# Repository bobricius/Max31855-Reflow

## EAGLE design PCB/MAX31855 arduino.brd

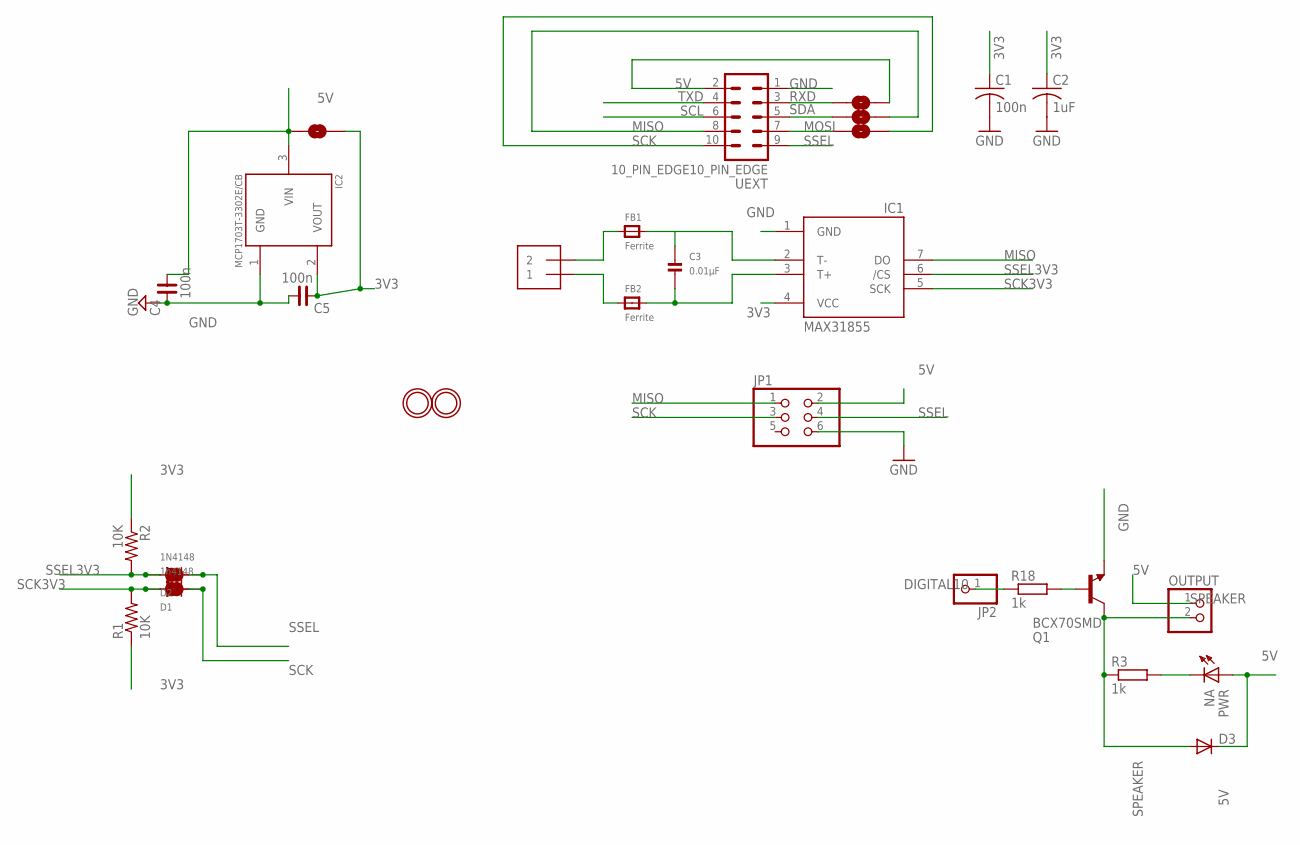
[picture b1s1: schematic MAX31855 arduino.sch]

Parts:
3V3: SOLDERJUMPERNO; SJ_2S-NO
C1: 100n; C0805K
C2: 1uF; C0805K
C3: 0.01µF; _0805
C4, C5: 100n; C0603
D1: 1n4148; SOD-323F
D2: 1N4148; SOD-323F
D3: DIODESOD; SOD-323
FB1, FB2: Ferrite; _0805
IC1: MAX31855; SO08
IC2: MCP1703T-3302E/CB; SOT23
J1: 1X2-3.5MM
JP1: PINHD-2X3; 2X03
JP2: PINHD-1X1; 1X01
MISO: SOLDERJUMPERNO; SJ_2S-NO
OUTPUT: PINHD-1X2; 1X02
PWR: NA; LED-0603
Q1: BCX70SMD; SOT23
R1, R2: 10K; R0603
R3, R18: 1k; R0603
SCK, SCK1, SCK2, SCK3: SOLDERJUMPERNO; SJ_2S-NO
U$3: 10_PIN_EDGE10_PIN_EDGE; 10_PIN_EDGE
U$4, U$5: MOUNTINGHOLE2.0; MOUNTINGHOLE_2.0_PLATED

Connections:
3V3: C1.1, C2.1, C5.2, IC1.4 (VCC), IC2.2 (VOUT), R1.1, R2.1, SCK3.1
5V: 3V3.2, C4.1, D3.1 (C), IC2.3 (VIN), JP1.2, OUTPUT.1, PWR.A, SCK3.2, U$3.2
DIGITAL10: JP2.1, R18.1
GND: C1.2, C2.2, C4.2, C5.1, IC1.1 (GND), IC2.1 (GND), JP1.6, Q1.2 (E), U$3.1
GND2: PWR.C, R3.2
MISO: IC1.7 (DO), JP1.1, MISO.2, U$3.8
MOSI: SCK.1, U$3.7
unnamed: FB1.1, J1.2
unnamed: C3.1, FB1.2, IC1.2 (T-)
unnamed: FB2.1, J1.1
unnamed: C3.2, FB2.2, IC1.3 (T+)
unnamed: Q1.1 (B), R18.2
RXD: 3V3.1, U$3.3
SCK: D1.C, JP1.3, SCK.2, SCK2.2, U$3.10
SCK3V3: D1.A, IC1.5 (SCK), R1.2, SCK2.1
SCL: U$3.6
SDA: MISO.1, U$3.5
SPEAKER: D3.2 (A), OUTPUT.2, Q1.3 (C), R3.1
SSEL: D2.C, JP1.4, SCK1.2, U$3.9
SSEL3V3: D2.A, IC1.6 (/CS), R2.2, SCK1.1
TXD: U$3.4

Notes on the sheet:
UEXT

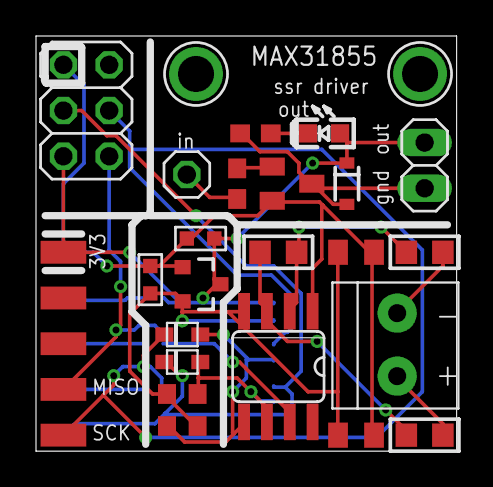
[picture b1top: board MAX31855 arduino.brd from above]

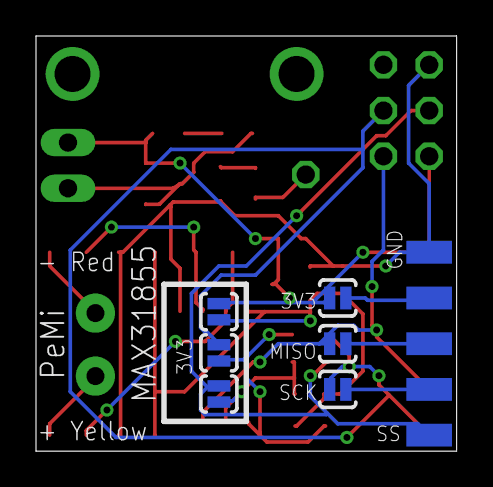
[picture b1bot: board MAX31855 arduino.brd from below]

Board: 2 copper layers, 23.4 x 23.1 mm, 31 parts (7 on the bottom side), 19 nets.

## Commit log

2014-11-12 :space_invader: Added .gitattributes & .gitignore files
2014-11-12 first upload

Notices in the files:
parts and their libraries:
SparkFun: Licensing: CC v3.0 Share-Alike You are welcome to use this library for commercial purposes.
